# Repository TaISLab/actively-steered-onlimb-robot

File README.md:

# Actively Steered Open On-Limb Robot 

On-limb robot designed to move along compliant cylindrical surfaces, such as human limbs or pipes. The platform integrates active steering, proprioceptive sensing, embedded control electronics, and compliant mechanical adaptation for locomotion on variable-diameter surfaces.

This repository accompanies the paper:

> Tobar-Subía-Contento, L.M.; Valenzuela, J.; Mandow, A.; Gómez-de-Gabriel, J.M. **"Actively Steered Open On-Limb Robot with Alignment Control and Online Diameter Estimation."** *Electronics* **2026**, *15*(17), 4028. https://doi.org/10.3390/electronics15174028

The main contribution is an integrated open on-limb robotic platform with active steering for real-time locomotion and alignment control. A generalized kinematic framework based on the complete Jacobian of the roller centers provides a geometric alignment variable for closed-loop steering correction and enables coordinate-independent online estimation of the supporting surface diameter from proprioceptive measurements.

Experiments on variable-diameter surfaces demonstrate the robot's ability to maintain centered longitudinal locomotion, handle non-symmetric link deflections, and estimate the local diameter online.

## Repository Contents

The repository is organized into two main sections:

```text
repository/
├── CAD/
├── electronics/
├── ControlSoftware/
├── MICIU+Cofinanciado+AEI.jpg
├── README.md
├── CITATION.cff
└── LICENSE
```

## Mechanical Design

The `mechanical/STL/` directory contains the mechanical components required to fabricate the robot structure using **additive manufacturing (3D printing)**.

The structural components of the prototype reported in the associated publication were fabricated using **polylactic acid (PLA)**.

### 3D Printing

Printing parameters may need to be adjusted depending on the printer, material, nozzle, layer height, and desired mechanical properties.

Users should verify dimensional tolerances and mechanical compatibility before final assembly.

## Electronics

The `electronics/` directory contains the electronic design files associated with the wearable robot prototype.

The electronics were designed using **KiCad** and the directory includes the complete project required to inspect the electrical schematic and PCB layout:

```text
electronics/
├── proyecto_robot_limbot.kicad_pro
├── proyecto_robot_limbot.kicad_sch
└── proyecto_robot_limbot.kicad_pcb
```

The files correspond to:

* **`.kicad_pro`** — KiCad project configuration.
* **`.kicad_sch`** — electronic schematic of the system.
* **`.kicad_pcb`** — printed circuit board (PCB) layout.

The project can be opened directly in **KiCad** using the `.kicad_pro` file.

Temporary files, local configuration files, autosaves, and backup directories generated automatically by KiCad are not included in the repository.

The electronic design files are provided to support reproduction, inspection, and further development of the hardware used in the research prototype.

# Control Software

This folder contains the software used for the control and experimental operation of the actively-steered on-limb robot.

The embedded control code was implemented for the ESP32-based controller and includes motor position control, servo control, sensor acquisition, signal filtering, serial communication, and experimental data transmission.

```text
ControlSoftware/
├── actively-steered-onlimb-robot.ino
├── robot_control_interface.py
```

## Citation

If you use or adapt the files, mechanical designs, or electronic designs contained in this repository for academic or research purposes, please cite the associated publication (see reference above) and, when appropriate, this repository.

GitHub users can use the **“Cite this repository”** option, or refer directly to the `CITATION.cff` file included in this repository, which contains the complete bibliographic metadata for both the article and the repository.

## Funding

This work is part of project PID2021-127221OB-I00 (CONCERTO — Control Colaborativo para Interacción física Empática entre RoboT y humanO), funded by MICIU/AEI/10.13039/501100011033/FEDER, UE.

## Acknowledgment

This repository accompanies academic research on wearable robotic systems and is provided to facilitate reproducibility and further research in the field.

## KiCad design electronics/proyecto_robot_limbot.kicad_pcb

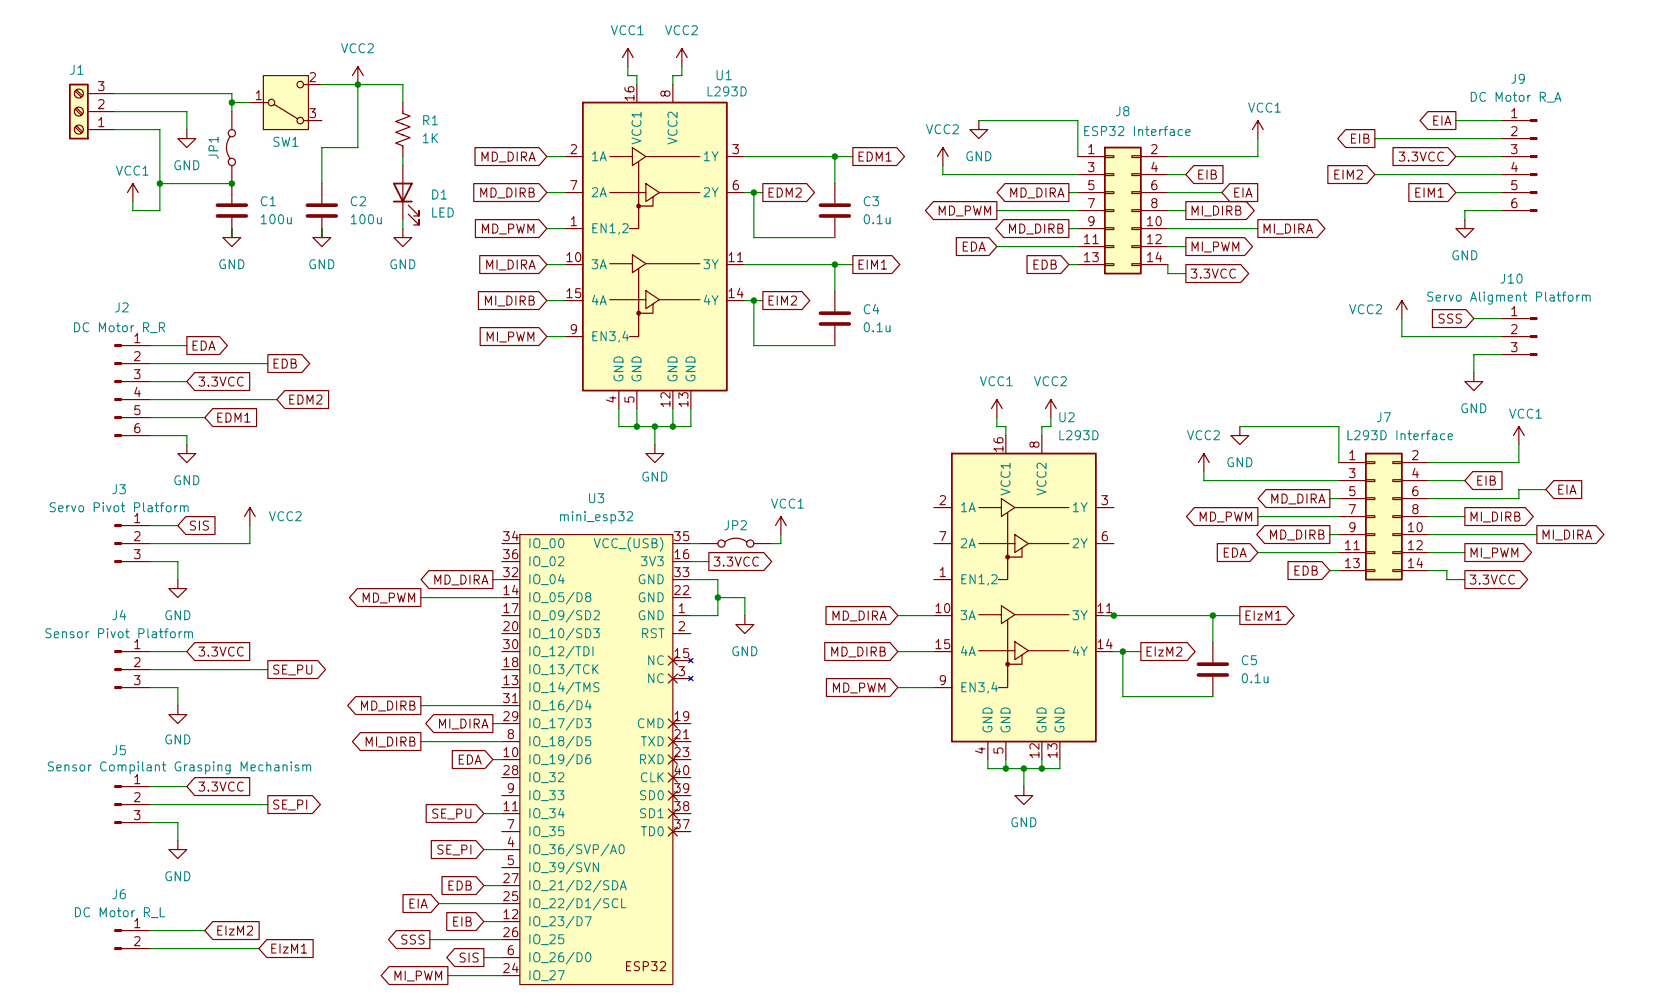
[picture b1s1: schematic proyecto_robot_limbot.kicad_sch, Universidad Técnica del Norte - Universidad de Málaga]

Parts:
C1, C2: 100u; C_Disc_D3.4mm_W2.1mm_P2.50mm
C3, C4, C5: 0.1u; C_Disc_D3.4mm_W2.1mm_P2.50mm
D1: LED; LED_D3.0mm_Clear
J1: TerminalBlock_MetzConnect_Type086_RT03403HBLC_1x03_P3.81mm_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
J2: DC Motor R_R; Molex_Micro-Latch_53254-0670_1x06_P2.00mm_Horizontal
J3: Servo Pivot Platform; Molex_Micro-Latch_53254-0370_1x03_P2.00mm_Horizontal
J4: Sensor Pivot Platform; Molex_Micro-Latch_53254-0370_1x03_P2.00mm_Horizontal
J5: Sensor Compilant Grasping Mechanism; Molex_Micro-Latch_53254-0370_1x03_P2.00mm_Horizontal
J6: DC Motor R_L; Molex_Micro-Latch_53254-0270_1x02_P2.00mm_Horizontal
J7: L293D Interface; PinSocket_2x07_P2.54mm_Vertical
J8: ESP32 Interface; PinHeader_2x07_P2.54mm_Vertical
J9: DC Motor R_A; Molex_Micro-Latch_53254-0670_1x06_P2.00mm_Horizontal
J10: Servo Aligment Platform; Molex_Micro-Latch_53254-0370_1x03_P2.00mm_Horizontal
JP1, JP2: TestPoint_2Pads_Pitch2.54mm_Drill0.8mm
R1: 1K; R_Axial_DIN0204_L3.6mm_D1.6mm_P5.08mm_Horizontal
SW1: SW_Slide-03_Wuerth-WS-SLTV_10x2.5x6.4_P2.54mm
U1, U2: L293D; DIP-16_W7.62mm_Socket_LongPads
U3: mini_esp32; ESP32_mini

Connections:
3.3VCC: J2.3, J4.1, J5.1, J7.14, J8.14, J9.3, U3.16 (3V3)
EDA: J2.1, J7.11, J8.11, U3.10 (IO_19/D6)
EDB: J2.2, J7.13, J8.13, U3.27 (IO_21/D2/SDA)
EDM1: C3.2, J2.5, U1.3 (1Y)
EDM2: C3.1, J2.4, U1.6 (2Y)
EIA: J7.6, J8.6, J9.1, U3.25 (IO_22/D1/SCL)
EIB: J7.4, J8.4, J9.2, U3.12 (IO_23/D7)
EIM1: C4.1, J9.5, U1.11 (3Y)
EIM2: C4.2, J9.4, U1.14 (4Y)
EIzM1: C5.2, J6.2, U2.11 (3Y)
EIzM2: C5.1, J6.1, U2.14 (4Y)
GND: C1.1, C2.1, D1.1 (K), J1.2, J2.6, J3.3, J4.3, J5.3, J7.1, J8.1, J9.6, J10.3, U1.4 (GND), U1.5 (GND), U1.12 (GND), U1.13 (GND), U2.4 (GND), U2.5 (GND), U2.12 (GND), U2.13 (GND), U3.1 (GND), U3.33 (GND)
MD_DIRA: J7.5, J8.5, U1.2 (1A), U2.10 (3A), U3.32 (IO_04)
MD_DIRB: J7.9, J8.9, U1.7 (2A), U2.15 (4A), U3.31 (IO_16/D4)
MD_PWM: J7.7, J8.7, U1.1 (EN1,2), U2.9 (EN3,4), U3.14 (IO_05/D8)
MI_DIRA: J7.10, J8.10, U1.10 (3A), U3.29 (IO_17/D3)
MI_DIRB: J7.8, J8.8, U1.15 (4A), U3.8 (IO_18/D5)
MI_PWM: J7.12, J8.12, U1.9 (EN3,4), U3.24 (IO_27)
unnamed: D1.2 (A), R1.1
unnamed: J1.3, JP1.2 (B), SW1.1 (B)
unnamed: JP2.1 (A), U3.35 (VCC_(USB))
SE_PI: J5.2, U3.4 (IO_36/SVP/A0)
SE_PU: J4.2, U3.11 (IO_34)
SIS: J3.1, U3.6 (IO_26/D0)
SSS: J10.1, U3.26 (IO_25)
VCC1: C1.2, J1.1, J7.2, J8.2, JP1.1 (A), JP2.2 (B), U1.16 (VCC1), U2.16 (VCC1)
VCC2: C2.2, J3.2, J7.3, J8.3, J10.2, R1.2, SW1.2 (C), U1.8 (VCC2), U2.8 (VCC2)

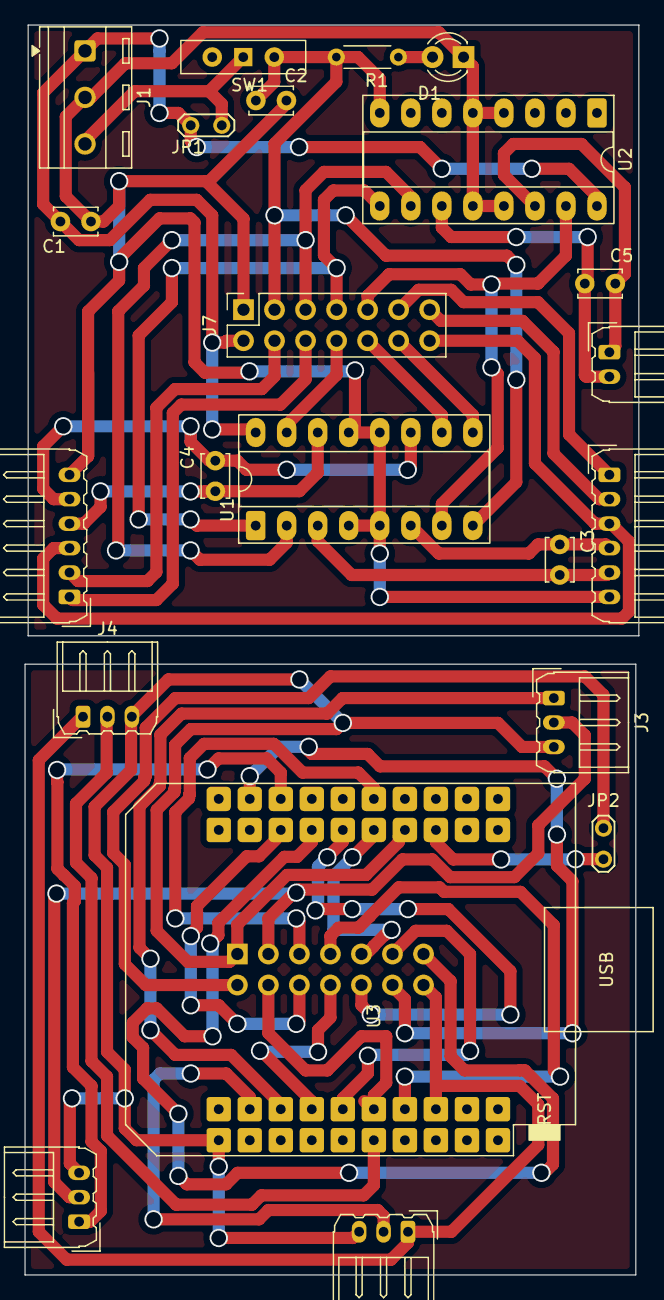
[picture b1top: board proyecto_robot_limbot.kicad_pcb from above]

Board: 2 copper layers, 50.3 x 102.3 mm, 23 parts (1 on the bottom side), 27 nets.

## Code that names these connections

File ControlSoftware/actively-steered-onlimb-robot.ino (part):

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#define E2A 22          // Encoder 2 canal A
#define E2B 23          // Encoder 2 canal B

#define SERVO_SSS 26    // Servo SSS
#define SERVO_SIS 25    // Servo SIS
#define SE_PI 36        // Potenciómetro PI (rho)
#define SE_PU 34        // Potenciómetro PU (theta)

long posicionEncoder1 = 0;
long posicionEncoder2 = 0;
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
